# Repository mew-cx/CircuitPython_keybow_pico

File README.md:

# README.txt
## Setup (DRAFT)
```bash
# using gitbash
cd /e
git clone --separate-git-dir=/c/mew/gits/dust_runtime_KEYBOW.git git@github.com:mew-cx/dust_runtime.git
mv dust_runtime/.git .
rmdir dust_runtime/
git checkout -f keybow_pico
```

## References
- https://shop.pimoroni.com/products/keybow
- https://pinout.xyz/pinout/keybow

- Revamping a Pi Keybow into a Pico Keybow.url
- https://codepope.dev/post/revamping-pi-keybow-into-pico-keybow/
- codepope-KeyBow-Pico-CircuitPython- CircuitPython code for driving a Keybow keyboard from Pimoroni using a Pi Pico (on a Pico.url
- https://github.com/codepope/KeyBow-Pico-CircuitPython

- The Keybow - Ben Madley's Blog.url
- https://benmadley.co.uk/2019/08/30/keybow.html

- https://redrobotics.co.uk/
- https://www.tindie.com/stores/redrobotics/
- https://www.tindie.com/products/redrobotics/pico-2-pi-adapter-board/
- https://github.com/RedRobotics

- https://github.com/DougieWougie/MouseJiggler

## Ideas
Add: mousejiggler ability
Add: some communications API from host system to set
- LED colors.
- keybindings.
- enable/disable mousejiggler

## Physical Key/LED numbering
```
+--------------------------+
|             K E Y B O W  |
+--------+--------+--------+
|        |        |        |
|    0   |    4   |    8   |
|        |        |        |
+--------+--------+--------+
|        |        |        |
|    1   |    5   |    9   |
|        |        |        |
+--------+--------+--------+
|        |        |        |
|    2   |    6   |   10   |
|        |        |        |
+--------+--------+--------+
|        |        |        |
|    3   |    7   |   11   |
|        |        |        |
+--------+--------+--------+
      USB

 +-----------+
 |     KEYBOW|
 | 0   4   8 |
 |           |
 | 1   5   9 |
 |           |
 | 2   6  10 |
 |           |
 | 3   7  11 |
 +-----------+
   USB
```

#eof

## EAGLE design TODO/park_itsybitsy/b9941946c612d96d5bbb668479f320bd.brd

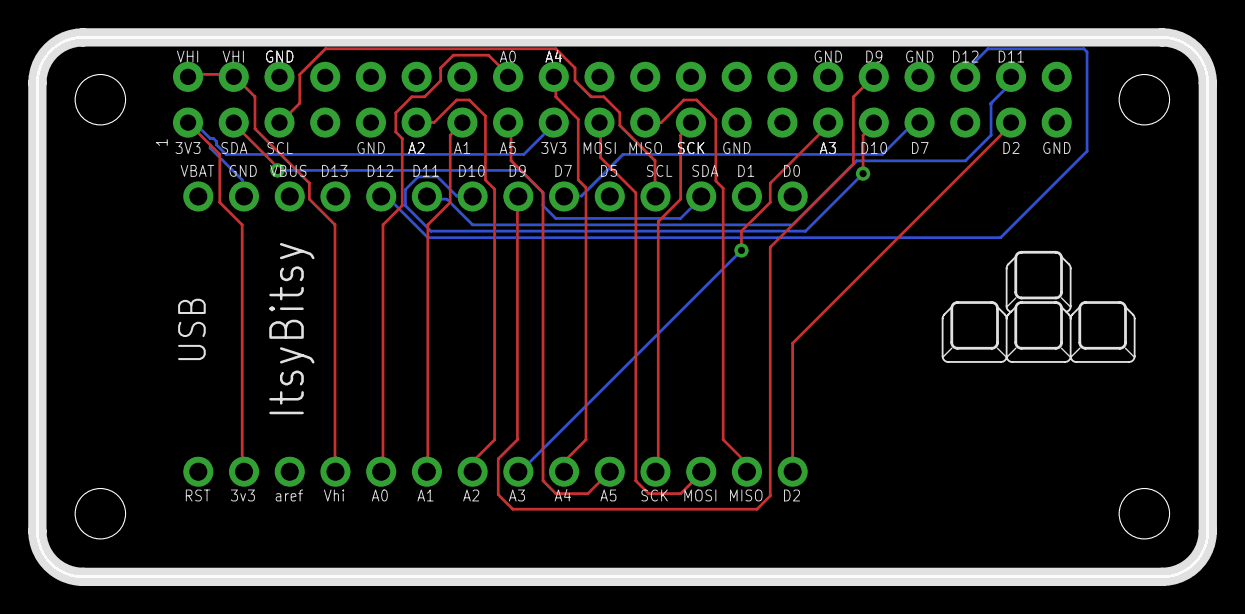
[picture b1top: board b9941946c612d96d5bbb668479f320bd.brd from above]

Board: 2 copper layers, 65.0 x 30.0 mm, 3 parts (0 on the bottom side), 20 nets.

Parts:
JP6, JP7: 1X14_ROUND70
RPI1: RASPBERRYPI_BPLUS_BONNETNODIM; PI_BONNET_NODIM

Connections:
+3V3: JP7.13, RPI1.1, RPI1.17
A0: JP7.10, RPI1.16
A1: JP7.9, RPI1.13
A2: JP7.8, RPI1.11
A3: JP7.7, RPI1.29
A4: JP7.6, RPI1.18
A5: JP7.5, RPI1.15
D2: JP7.1, RPI1.37
D7: JP6.9, RPI1.33
D9: JP6.8, RPI1.32
D10: JP6.7, RPI1.31
D11: JP6.6, RPI1.38
D12: JP6.5, RPI1.36
GND: JP6.2, RPI1.6, RPI1.9, RPI1.14, RPI1.20, RPI1.25, RPI1.30, RPI1.34, RPI1.39
MISO: JP7.2, RPI1.21
MOSI: JP7.3, RPI1.19
SCK: JP7.4, RPI1.23
SCL: JP6.11, RPI1.5
SDA: JP6.12, RPI1.3
VHI: JP7.11, RPI1.2, RPI1.4

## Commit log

2022-05-23 add empty .git* files
2022-05-23 .gitattributes
2023-02-27 .gitignore
2023-02-27 update __repo__
2023-02-27 spi_test : adjust for keybow SPI pins
2023-02-27 code.py
2023-02-27 copy spi_test.py from dotstar branch
2023-02-27 README.txt
2023-02-27 add __repo__ & __version__
2023-02-27 wget status_multi_dotstar_rainbow
    https://raw.githubusercontent.com/adafruit/Adafruit_Learning_System_Guides/main/CircuitPython_Templates/status_multi_dotstar_rainbow/code.py
2023-02-27 cew_editkeys : adjust button colors
2023-02-27 add keybow_pico.py : concat a bunch of other files
    more macropad_hid_example.py keybow_dotstar.py kewbowcode.py adafruit_macropad_demo.py > keybow_pico.py
2023-02-27 refresh lib/ to 7.3.1 (7.x-mpy-20220630)
2023-02-27 wget KeyBow-Pico-CircuitPython
    https://raw.githubusercontent.com/codepope/KeyBow-Pico-CircuitPython/master/kewbowcode.py
2023-02-27 README.txt : add urls
2023-02-27 add keybow_pico_cew_editkeys.py
2023-02-27 move clear() higher in file
2023-02-27 spi_test : refinements
2023-02-27 minor refactor
2023-02-27 wget status_multi_dotstar_rgb
    https://raw.githubusercontent.com/adafruit/Adafruit_Learning_System_Guides/main/CircuitPython_Templates/status_multi_dotstar_rgb/code.py
2023-02-27 more refactoring
2023-02-27 rm unneeded from dotstar merge
2023-02-27 raspberry_pi_pico__e6611cb697619e28.txt
2023-02-27 dust_dotstar : try @atexit.register decorator
2023-02-27 wget macropad_hid_example.py
    https://learn.adafruit.com/pages/22581/elements/3112363/download -> macropad_hid_example.py
    https://learn.adafruit.com/key-pad-matrix-scanning-in-circuitpython/keys-one-key-per-pin
2023-02-27 simple reformatting
2023-02-27 move clear()
2023-02-27 wget macropad_example.py
    https://learn.adafruit.com/pages/22581/elements/3099042/download -> macropad_example.py
    https://learn.adafruit.com/key-pad-matrix-scanning-in-circuitpython/keys-one-key-per-pin
2023-02-27 combine macropad*_example.py
2023-02-27 keybow_dotstar : works on keybow_pico
2023-02-27 adjust key events to match keymap
2023-02-27 split out HandleKey()
2023-02-27 add required libs
2023-02-27 add spi_test.py from asbuilt
2023-02-27 combine KEY_PINS & KEYCODES into KEYDATA
2023-02-27 LICENSE
2023-02-27 reorg/adjust imports
2023-02-27 TODO.txt
2023-02-27 wget status_led_one_dotstar_rainbow
    https://raw.githubusercontent.com/adafruit/Adafruit_Learning_System_Guides/main/CircuitPython_Templates/status_led_one_dotstar_rainbow/code.py
2023-02-27 rename dust_dotstar.py to keybow_dotstar.py
2023-02-27 wget status_led_one_dotstar_rgb
    https://raw.githubusercontent.com/adafruit/Adafruit_Learning_System_Guides/main/CircuitPython_Templates/status_led_one_dotstar_rgb/code.py
2023-02-27 rework clear()
2023-02-27 code.py : import keybow_pico_cew_editkeys.py
2023-02-27 dust_dotstar : working on dust
2023-02-27 wget dotstar_simpletest.py
    https://raw.githubusercontent.com/adafruit/Adafruit_CircuitPython_DotStar/main/examples/dotstar_simpletest.py
2023-02-27 GITDIR.txt
2023-02-27 timing.txt
2023-02-27 split out kdata. reorg dots
2023-02-27 wget adafruit_macropad_demo.py
    https://raw.githubusercontent.com/adafruit/Adafruit_Learning_System_Guides/main/Adafruit_MacroPad/MacroPad/code.py -> adafruit_macropad_demo.py
    https://learn.adafruit.com/adafruit-macropad-rp2040/keypad
2023-02-27 keybow_pico.py
2023-02-27 cew_editkeys : implement the full 12-key config
2023-02-27 refresh raspberry_pi_pico__e6611cb697619e28.txt
2023-02-27 TODO.txt
    (cherry picked from commit 97a42cb4bc1973a69dc480579889bbf26ce9f88a)
2023-02-27 bump copyright date for 2023
2023-02-27 README.txt : consolidate & edit
2023-02-27 rm cruft : TODO.txt, spi_test.py, timing.txt
2023-02-27 add boot.py
2023-02-27 rm old obsolete keybow_pico.py
2023-04-22 from_actual_device
2023-09-15 info before upgrade to CircuitPython v8.2.6
2023-09-16 rm cruft
2023-09-16 rm old 7.3.2 libraries
2023-09-16 .git_
2023-09-16 __init__.py
2023-09-16 boot.py : kittykey selects development mode
2023-09-16 keybow_pico_cew_editkeys.py 0.2.5.5
2023-09-16 mv README.txt README.md
2023-09-16 README.md
2023-09-30 add TODO/
2023-09-30 add _top/
2023-10-09 keys.events.get_into()

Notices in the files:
parts and their libraries:
microbuilder: This work is placed in the public domain, and may be freely used for commercial and non-commercial work with the following conditions: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
